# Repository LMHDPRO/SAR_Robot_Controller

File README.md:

# SAR Robot Controller 1.6

**Mobile search-and-rescue robotics platform**

A Python/PySide6 desktop controller for a differential-drive AGV, a servo-driven arm, the COCO handheld controller, two ESP32-S3 IP cameras, and a COIN-D6 LiDAR. The repository includes firmware, editable CAD, engineering drawings, and PCB fabrication files.

[Software modules](#software-modules) · [Hardware and firmware](#hardware-and-firmware) · [Mechanical design](#mechanical-design) · [Quick start](#quick-start)

## Control and sensing

| Workspace | What it does |
| --- | --- |
| **AGV** | Manual driving, wheel odometry, BNO055 heading hold and precision turns, wheel calibration, and a 50 cm ground-distance calibration. Global controls manage PC/COCO ownership, power, STOP, and E-STOP. |
| **Arm V7** | 3D preview, joint and Cartesian controls, gripper control, and path preview. Forward kinematics (FK) calculates the tool position from joint angles. Inverse kinematics (IK) solves for joint angles to reach an XYZ target. The four-axis model is separate from wrist rotation and gripper commands. |
| **IP Cameras · ArUco** | Independent AGV and arm video feeds with ArUco ID detection. Camera calibration and the physical marker size enable camera-frame pose and distance estimates. The AGV camera uses a saved reference for a supervised approach to ArUco ID 12. The full ArUco sequence starts PICK after alignment and fresh zero motor PWM. PICK and UNPICK also have individual controls. |
| **LiDAR / SLAM** | Live COIN-D6 scans, raw recording and offline replay, and experimental local 2D mapping. Scan matching can use encoder and IMU motion estimates. The workspace provides range summaries, guidance back to a saved pose, and NPZ/PNG map export. See the [LiDAR and SLAM guide](LIDAR_SLAM.md). |
| **Routines** | Build and save ordered programs with encoder/IMU moves, precision turns, waits, joint poses, XYZ poses via IK, and ArUco alignment. Global STOP cancels the running routine. |

In **Brazo · V7 → Control → Perfil articular**, **Lineal** is the startup default. Select **Quíntico** to preview a rest-to-rest joint move with the FK sliders or **Home**. The selected profile also applies to physical Home, manual pose commands, and arm poses in routines, including pickup and placement. Live PC slider commands use linear interpolation.

In **JOINTS**, move the arm joystick up or down to select a channel and return it to center before selecting again. Hold the deadman and turn the encoder for one degree per click. In the menu, use the AGV joystick to highlight **HOME**, **PICK**, **UNPICK**, or **ARUCO**, then press the encoder to accept. Center the sticks and hold the deadman to run the selected action. Releasing it cancels motion. **E-STOP** takes effect on encoder press and displays the latch state from Python. Reset it from the PC.

On COCO, release the deadman and hold **B** to open the menu. Turn the encoder on **IK** to select **CCD**, **Newton-Raphson**, or **Levenberg-Marquardt** for Cartesian moves in **DUAL** and **TCP**. On **PROFILE**, turn the encoder clockwise for **QUINTIC** or counterclockwise for **LINEAR**. The profile applies to arm moves from COCO, including **JOINTS**. COCO starts with CCD and LINEAR. These menu options use the updated desktop app, and physical quintic moves require SAR_AGV firmware with `ARMQ` support.

## Software modules

| Area | Files and responsibilities |
| --- | --- |
| **Application and drive** | [app.py](app.py) launches the desktop UI and coordinates device links, telemetry, motion, and stops. [core.py](core.py) contains drive geometry, odometry, motion primitives, and calibration logic. [defaults.py](defaults.py) defines startup settings. |
| **Arm and routines** | [arm.py](arm.py) implements Denavit–Hartenberg FK and numerical XYZ IK. [robotarm_v7.py](robotarm_v7.py) provides the V7 interface and 3D planning tools. [arm_workspace.py](arm_workspace.py) connects V7 to AGV commands and global stops. [routine_blocks.py](routine_blocks.py) handles execution and completion for arm and ArUco blocks. |
| **Camera and vision** | [cameras.py](cameras.py) manages the two camera panels and capture processes. [camera_worker.py](camera_worker.py) reads frames, detects markers, and estimates pose. [camera_connection.py](camera_connection.py) handles arm-camera discovery and stream activation. [camera_calibration.py](camera_calibration.py) calibrates AGV camera intrinsics from checkerboard images. |
| **Alignment and handling** | [aruco_alignment.py](aruco_alignment.py) evaluates marker distance, reference alignment, and orientation during the approach. [pickup_sequence.py](pickup_sequence.py) sequences the arm and gripper for pickup and release. |
| **LiDAR acquisition and mapping** | [coind6/](coind6/) handles TCP input, replay, packet decoding, and scan assembly. [lidar_workspace.py](lidar_workspace.py) manages the scan and map UI. [slam.py](slam.py) performs local scan matching using iterative closest point (ICP). |
| **LiDAR calibration and display** | [lidar_calibration.py](lidar_calibration.py) assists with mount alignment and masking. [lidar_filters.py](lidar_filters.py) excludes chassis returns and configured angular sectors. [lidar_guidance.py](lidar_guidance.py) calculates sector ranges and offsets to a saved pose. [lidar_exploration.py](lidar_exploration.py) tracks observed cells for display. [map_export.py](map_export.py) saves map points, trajectory, and metadata. |

## Hardware and firmware

| Component | Function | Repository assets |
| --- | --- | --- |
| **AGV controller PCB** | ESP32-based drive controller with wheel encoders, a BNO055 IMU, relays, and a physical E-STOP input. The PCA9685 drives six arm and gripper servo channels. | [KiCad and fabrication files](Hardware/AGV_PCB/) · [Arduino firmware](firmware/SAR_AGV/) |
| **COCO handheld PCB** | Arduino Nano ESP32 gamepad with joysticks, rotary encoder, OLED, and a deadman input. Modes cover joint control, combined arm and drive control, Cartesian tool control, and AGV driving. | [KiCad and fabrication files](Hardware/GAMEPAD_ESP32/) · [Arduino firmware](firmware/COCO_Controller/) |
| **ESP32-S3-CAM** | IP video feeds for the AGV and arm. The included camera sketch serves MJPEG and is configured for the ESP32-S3-EYE pin map. | [Camera firmware](firmware/CameraWebServer_UAM/) · [Fusion 360 camera enclosure](CAD/Fusion360/ESP32S3_CAM_Case.f3z) · [STEP camera enclosure](CAD/STEP/Botcillo_ESP32S3_CAM.step) |
| **COIN-D6 LiDAR** | External 2D scanner connected directly to the PC through a dedicated TCP bridge. | [STL mount](CAD/STL/LIDAR_AGV.stl) · [Setup and calibration](LIDAR_SLAM.md) |

Both PCB folders contain KiCad schematics and layouts, Gerber and drill files, and production exports with BOMs and component positions.

## Mechanical design

| Assembly | Editable Fusion 360 model | PDF engineering drawing |
| --- | --- | --- |
| AGV chassis | [AGV 2026](CAD/Fusion360/AGV_2026.f3z) | [AGV drawing](CAD/Drawings/AGV_Drawing.pdf) |
| Robotic arm | [Robotic Arm](CAD/Fusion360/Robotic_Arm.f3d) | [Arm drawing](CAD/Drawings/RoboticArm_Drawing.pdf) |
| COCO enclosure | [Gamepad Bot 2026](CAD/Fusion360/GAMEPAD_BOT_2026.f3z) | [Gamepad drawing](CAD/Drawings/GAMEPAD_BOT_Drawing.pdf) |
| SAR victim target | [Victim SAR 2026](CAD/Fusion360/Victim_SAR_2026.f3d) | [Target drawing](CAD/Drawings/Victim_SAR_Drawing.pdf) |

[Printable STL parts](CAD/STL/) · [Arm URDF/Xacro and meshes](Brazo_Robotico_ROS2_description/) · [Tipping stability report](CAD/Reports/Tipping%20Stability%20Analysis%20Report.pdf)

## Quick start

Use 64-bit Python 3.11 or 3.12. From the repository root in PowerShell:

```powershell
python -m venv .venv
.\.venv\Scripts\python.exe -m pip install "PySide6==6.8.3" "pyqtgraph==0.14.0" "numpy>=1.26,<3" matplotlib pyserial "opencv-contrib-python-headless>=4.10,<6"
.\.venv\Scripts\python.exe app.py
```

For firmware uploads, set the Wi-Fi credentials locally and select the matching board and camera pin map. For COCO, select **Arduino Nano ESP32** with **Pin Numbering → By GPIO number (legacy)**.

| Device | Connection from the PC |
| --- | --- |
| AGV | TCP 4211. Set the AGV IP in the global toolbar. |
| COCO | TCP 4210. Set the COCO IP in the global toolbar. |
| IP cameras | Enter the stream URL for each camera. The included sketch serves MJPEG at `http://<camera-ip>:81/stream`. For an arm camera running CameraIP-compatible firmware, enter its base URL to discover and activate the stream. |
| COIN-D6 | Enter the external bridge IP and TCP port in **LiDAR / SLAM**. The default port is 9000. |

For ArUco alignment, select the camera calibration, enter the printed marker's measured side length, and save a reference for ID 12. Verify the approach and arm path on the physical robot with STOP within reach. Arm positions reported by the controller are PWM-based estimates. LiDAR SLAM provides a local point map for operator guidance and analysis.

## Tests

Run the [software test suite](tests/) for drive and arm logic, camera calibration and ArUco, routines, LiDAR decoding, SLAM, and simulated links.

```powershell
.\.venv\Scripts\python.exe -m unittest discover -s tests -v
```

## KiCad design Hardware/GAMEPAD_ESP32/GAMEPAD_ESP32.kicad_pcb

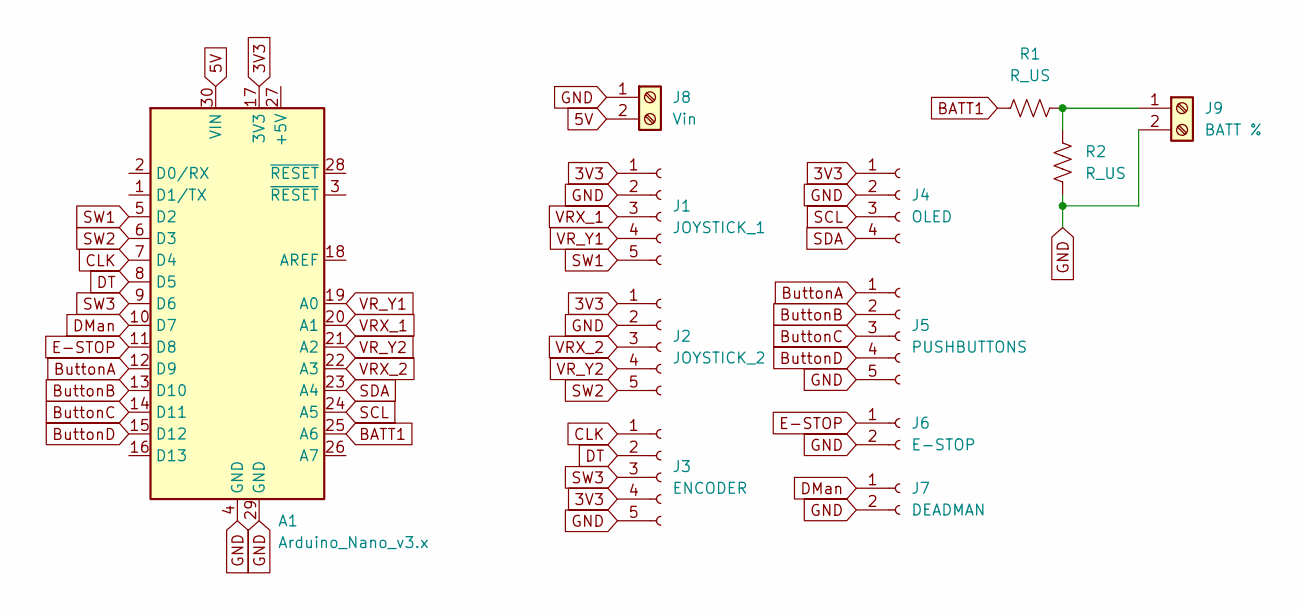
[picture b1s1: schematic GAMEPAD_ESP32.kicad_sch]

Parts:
A1: Arduino_Nano_v3.x; Arduino_Nano
J1: JOYSTICK_1; PinSocket_1x05_P2.54mm_Vertical
J2: JOYSTICK_2; PinSocket_1x05_P2.54mm_Vertical
J3: ENCODER; PinSocket_1x05_P2.54mm_Vertical
J4: OLED; PinSocket_1x04_P2.54mm_Vertical
J5: PUSHBUTTONS; PinSocket_1x05_P2.54mm_Vertical
J6: E-STOP; PinSocket_1x02_P2.54mm_Vertical
J7: DEADMAN; PinSocket_1x02_P2.54mm_Vertical
J8: Vin; TerminalBlock_Phoenix_MKDS-1,5-2-5.08_1x02_P5.08mm_Horizont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
J9: BATT %; TerminalBlock_Phoenix_MKDS-1,5-2-5.08_1x02_P5.08mm_Horizont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
R1, R2: R_US; R_Axial_DIN0207_L6.3mm_D2.5mm_P10.16mm_Horizontal

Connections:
3V3: A1.17 (3V3), J1.1, J2.1, J3.4, J4.1
5V: A1.30 (VIN), J8.2
BATT1: A1.25 (A6), R1.1
ButtonA: A1.12 (D9), J5.1
ButtonB: A1.13 (D10), J5.2
ButtonC: A1.14 (D11), J5.3
ButtonD: A1.15 (D12), J5.4
CLK: A1.7 (D4), J3.1
DMan: A1.10 (D7), J7.1
DT: A1.8 (D5), J3.2
E-STOP: A1.11 (D8), J6.1
GND: A1.4 (GND), A1.29 (GND), J1.2, J2.2, J3.5, J4.2, J5.5, J6.2, J7.2, J8.1, J9.2, R2.1
unnamed: J9.1, R1.2, R2.2
SCL: A1.24 (A5), J4.3
SDA: A1.23 (A4), J4.4
SW1: A1.5 (D2), J1.5
SW2: A1.6 (D3), J2.5
SW3: A1.9 (D6), J3.3
VRX_1: A1.20 (A1), J1.3
VRX_2: A1.22 (A3), J2.3
VR_Y1: A1.19 (A0), J1.4
VR_Y2: A1.21 (A2), J2.4

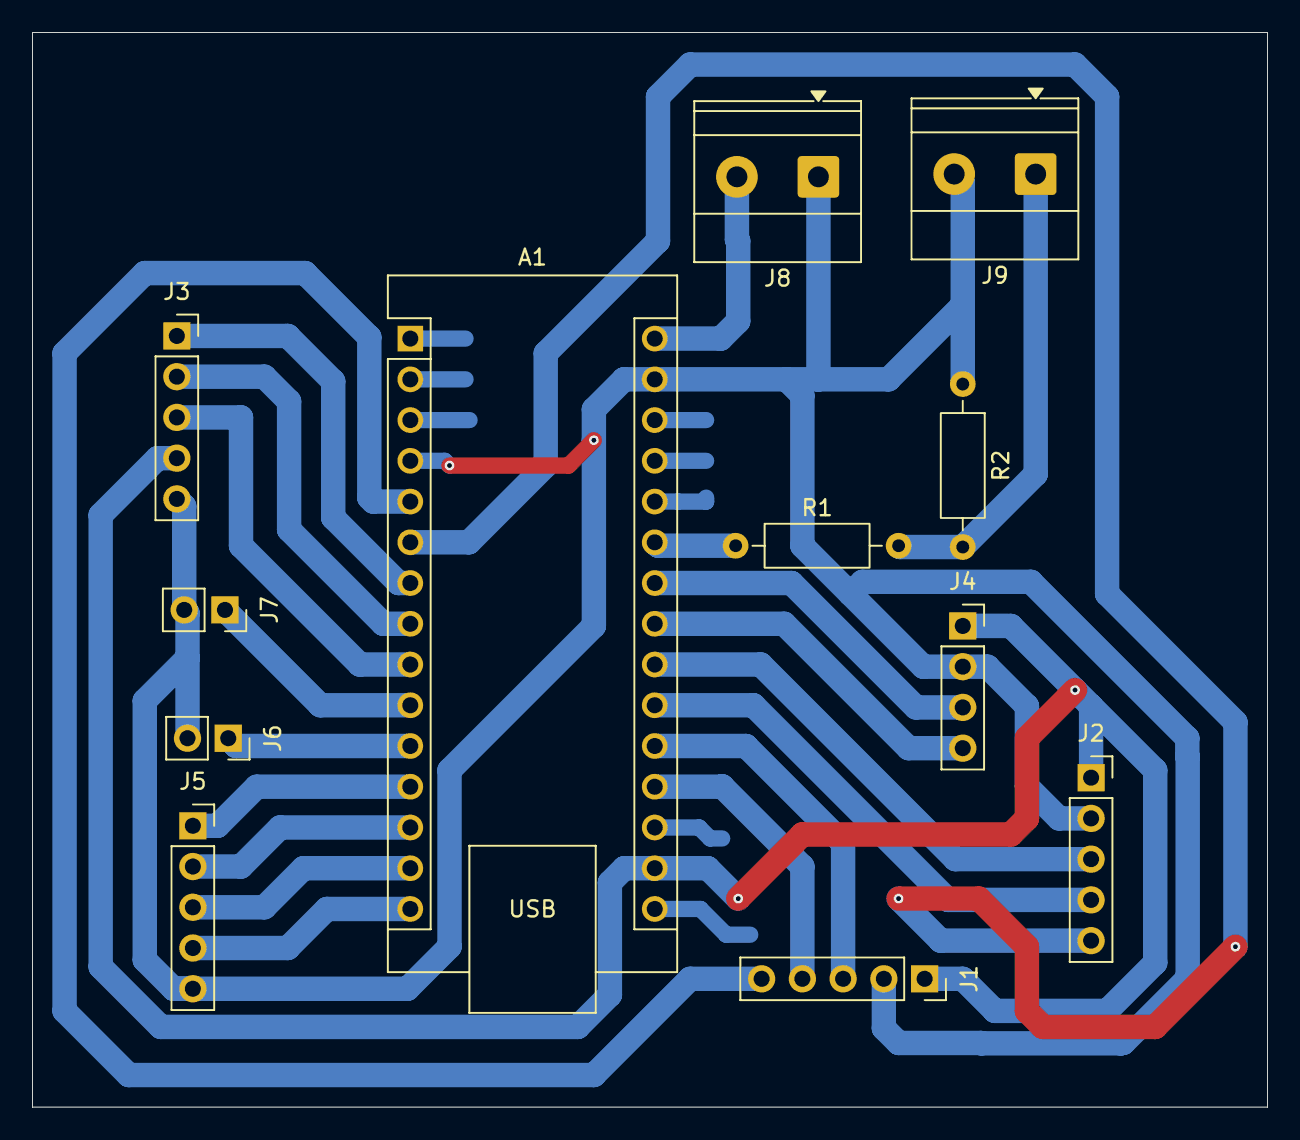
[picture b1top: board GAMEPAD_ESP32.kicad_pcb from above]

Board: 2 copper layers, 77.0 x 67.0 mm, 12 parts (0 on the bottom side), 22 nets.

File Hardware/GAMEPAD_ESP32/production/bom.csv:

Designator,Footprint,Quantity,Value,LCSC Part #
A1,Arduino_Nano,1,Arduino_Nano_v3.x,
J1,PinSocket_1x05_P2.54mm_Vertical,1,JOYSTICK_1,
J2,PinSocket_1x05_P2.54mm_Vertical,1,JOYSTICK_2,
J3,PinSocket_1x05_P2.54mm_Vertical,1,ENCODER,
J4,PinSocket_1x04_P2.54mm_Vertical,1,OLED,
J5,PinSocket_1x05_P2.54mm_Vertical,1,PUSHBUTTONS,
J6,PinSocket_1x02_P2.54mm_Vertical,1,E-STOP,
J7,PinSocket_1x02_P2.54mm_Vertical,1,DEADMAN,
J8,"TerminalBlock_Phoenix_MKDS-1,5-2-5.08_1x02_P5.08mm_Horizontal",1,Vin,
J9,"TerminalBlock_Phoenix_MKDS-1,5-2-5.08_1x02_P5.08mm_Horizontal",1,BATT %,
"R1, R2",R_Axial_DIN0207_L6.3mm_D2.5mm_P10.16mm_Horizontal,2,R_US,

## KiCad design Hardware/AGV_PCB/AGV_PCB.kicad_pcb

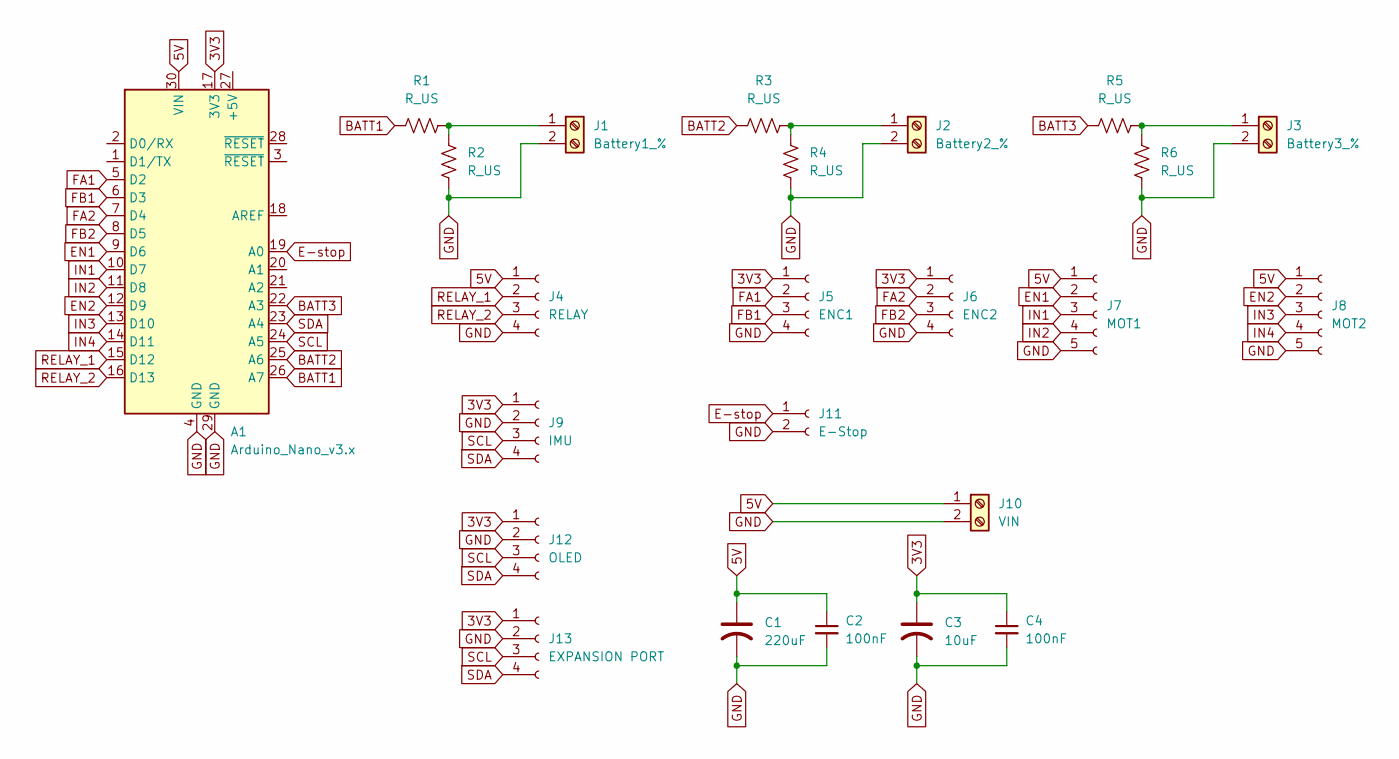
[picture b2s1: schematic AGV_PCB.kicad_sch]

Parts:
A1: Arduino_Nano_v3.x; Arduino_Nano
C1: 220uF; C_Radial_D10.0mm_H16.0mm_P5.00mm
C2, C4: 100nF; C_Disc_D3.8mm_W2.6mm_P2.50mm
C3: 10uF; C_Radial_D5.0mm_H7.0mm_P2.00mm
J1: Battery1_%; TerminalBlock_Phoenix_MKDS-1,5-2-5.08_1x02_P5.08mm_Horizont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
J2: Battery2_%; TerminalBlock_Phoenix_MKDS-1,5-2-5.08_1x02_P5.08mm_Horizont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
J3: Battery3_%; TerminalBlock_Phoenix_MKDS-1,5-2-5.08_1x02_P5.08mm_Horizont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
J4: RELAY; JST_XH_B4B-XH-A_1x04_P2.50mm_Vertical
J5: ENC1; JST_XH_B4B-XH-A_1x04_P2.50mm_Vertical
J6: ENC2; JST_XH_B4B-XH-A_1x04_P2.50mm_Vertical
J7: MOT1; JST_XH_B5B-XH-A_1x05_P2.50mm_Vertical
J8: MOT2; JST_XH_B5B-XH-A_1x05_P2.50mm_Vertical
J9: IMU; JST_XH_B4B-XH-A_1x04_P2.50mm_Vertical
J10: VIN; TerminalBlock_Phoenix_MKDS-1,5-2-5.08_1x02_P5.08mm_Horizont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
J11: E-Stop; JST_XH_B2B-XH-A_1x02_P2.50mm_Vertical
J12: OLED; JST_XH_B4B-XH-A_1x04_P2.50mm_Vertical
J13: EXPANSION PORT; JST_XH_B4B-XH-A_1x04_P2.50mm_Vertical
R1, R2, R3, R4, R5, R6: R_US; R_Axial_DIN0204_L3.6mm_D1.6mm_P7.62mm_Horizontal

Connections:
3V3: A1.17 (3V3), C3.1, C4.1, J5.1, J6.1, J9.1, J12.1, J13.1
5V: A1.30 (VIN), C1.1, C2.1, J4.1, J7.1, J8.1, J10.1
BATT1: A1.26 (A7), R1.1
BATT2: A1.25 (A6), R3.1
BATT3: A1.22 (A3), R5.1
E-stop: A1.19 (A0), J11.1
EN1: A1.9 (D6), J7.2
EN2: A1.12 (D9), J8.2
FA1: A1.5 (D2), J5.2
FA2: A1.7 (D4), J6.2
FB1: A1.6 (D3), J5.3
FB2: A1.8 (D5), J6.3
GND: A1.4 (GND), A1.29 (GND), C1.2, C2.2, C3.2, C4.2, J1.2, J2.2, J3.2, J4.4, J5.4, J6.4, J7.5, J8.5, J9.2, J10.2, J11.2, J12.2, J13.2, R2.1, R4.1, R6.1
IN1: A1.10 (D7), J7.3
IN2: A1.11 (D8), J7.4
IN3: A1.13 (D10), J8.3
IN4: A1.14 (D11), J8.4
unnamed: J1.1, R1.2, R2.2
unnamed: J2.1, R3.2, R4.2
unnamed: J3.1, R5.2, R6.2
RELAY_1: A1.15 (D12), J4.2
RELAY_2: A1.16 (D13), J4.3
SCL: A1.24 (A5), J9.3, J12.3, J13.3
SDA: A1.23 (A4), J9.4, J12.4, J13.4

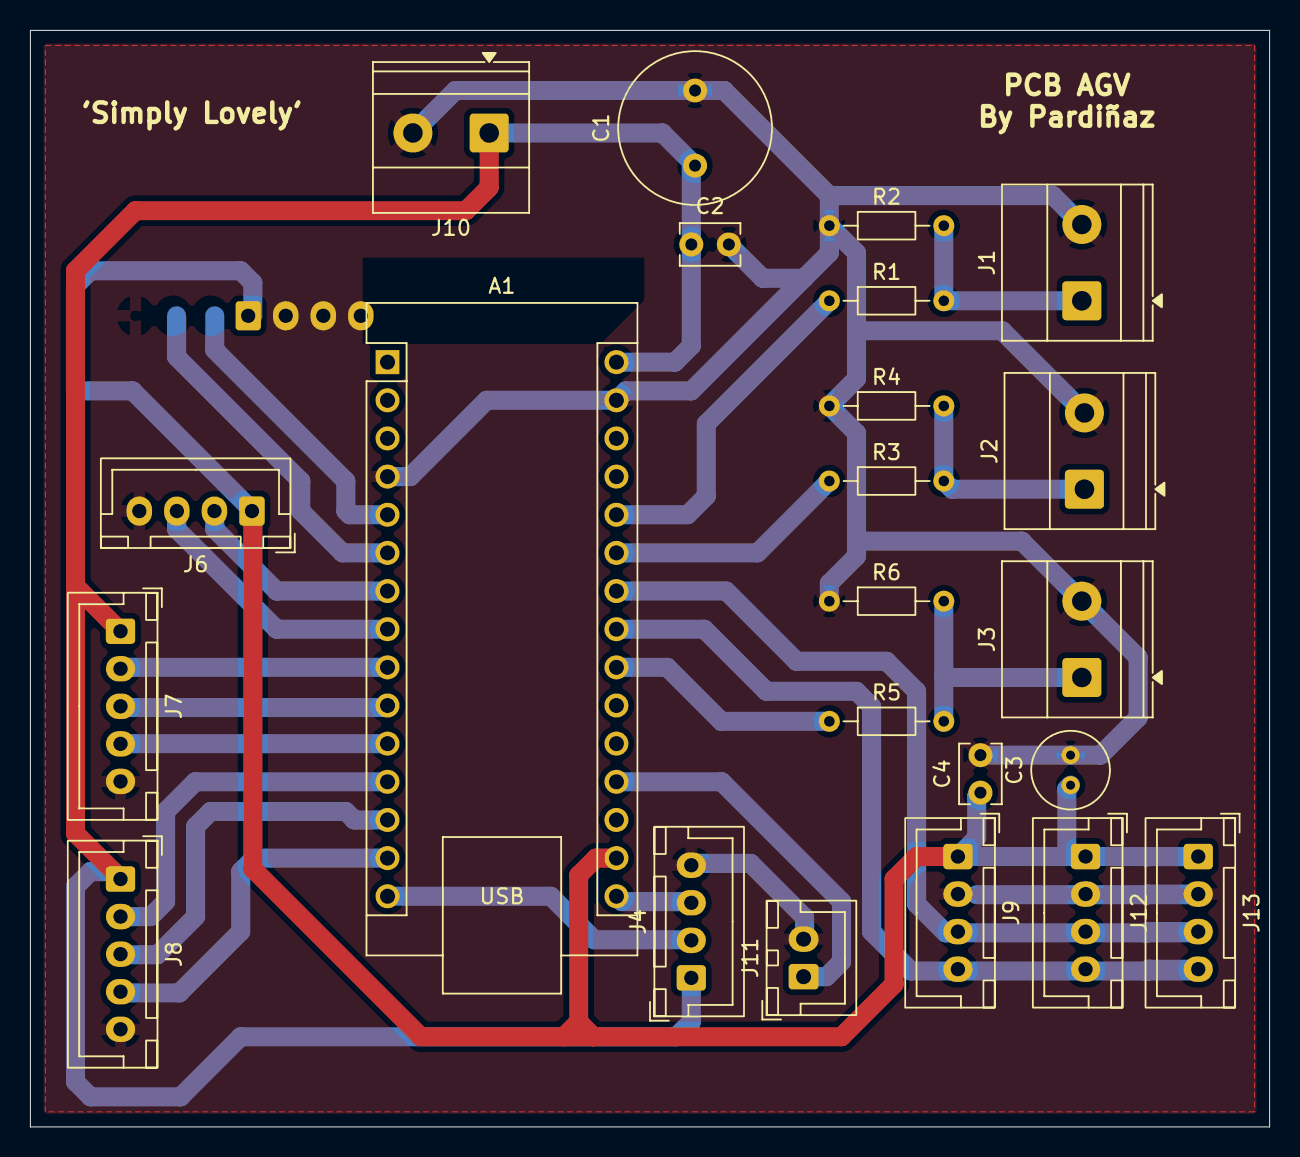
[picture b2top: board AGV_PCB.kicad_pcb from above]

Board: 2 copper layers, 82.5 x 73.0 mm, 24 parts (1 on the bottom side), 24 nets.

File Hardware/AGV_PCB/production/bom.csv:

Designator,Footprint,Quantity,Value,LCSC Part #
A1,Arduino_Nano,1,Arduino_Nano_v3.x,
J1,"TerminalBlock_Phoenix_MKDS-1,5-2-5.08_1x02_P5.08mm_Horizontal",1,Battery1_%,
J10,"TerminalBlock_Phoenix_MKDS-1,5-2-5.08_1x02_P5.08mm_Horizontal",1,VIN,
J11,PinHeader_1x02_P2.54mm_Vertical,1,E-Stop,
J12,PinHeader_1x04_P2.54mm_Vertical,1,OLED,
J2,"TerminalBlock_Phoenix_MKDS-1,5-2-5.08_1x02_P5.08mm_Horizontal",1,Battery2_%,
J3,"TerminalBlock_Phoenix_MKDS-1,5-2-5.08_1x02_P5.08mm_Horizontal",1,Battery3_%,
J4,PinHeader_1x04_P2.54mm_Vertical,1,RELAY,
J5,PinHeader_1x04_P2.54mm_Vertical,1,ENC1,
J6,PinHeader_1x04_P2.54mm_Vertical,1,ENC2,
J7,PinHeader_1x05_P2.54mm_Vertical,1,MOT1,
J8,PinHeader_1x05_P2.54mm_Vertical,1,MOT2,
J9,PinHeader_1x04_P2.54mm_Vertical,1,IMU,
"R1, R2, R3, R4, R5, R6",R_Axial_DIN0204_L3.6mm_D1.6mm_P7.62mm_Horizontal,6,R_US,
